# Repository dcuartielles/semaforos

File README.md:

# Aprendiendo electrónica y programación utilizando semáforos
*(título propuesto por La Hora Maker, aka Cesar García)*

Proyecto colectivo de realizar semáforos en la mayor cantidad de modos posible.

*PCB de semáforo por Gustavo Reynaga*

## Lista de Ejemplos

* Jose Antonio Vacas, @javacasm: introducción (aquí forzando)
* Julián Caro Linares, @jcarolinares: FPGA
* David Cuartielles, @dcuartielles: Arduino
* Raúl Lapeira Herrero, @raul_lapeira: Skypic
* Josemanu, @Ardumania_Jmanu: CircuitPython
* Jorge, @akirasan: ATtiny85 + Arduino como programador
* Jorge, @akirasan: Blender
* Jorge, @akirasan: Processing
* Luis Miranda, @LuisMirandaAceb: 555s y componentes discretos
* María L, @tecnoloxia: semáforo mecánico
* María L, @tecnoloxia: Scratch
* David Estévez, @DEFrobotics: RPi + WiringPi
* David Estévez, @DEFrobotics: Semáforo con robot industrial (por los loles)
* Nuria y Jorfru, @nuria_pp: DGT
* Gustavo Reynaga, @gsreynaga: [PCB personalizada con KiCad.](https://github.com/dcuartielles/semaforos/tree/master/ejemplos/KiCad)  [hulkco](https://github.com/hulkco?tab=repositories)
* Iraisy Figueroa, @Iraisy: circuito textil con 555
* Iraisy Figueroa, @Iraisy: S4A
* Alex Corvis, @AlexCorvis84: Node-RED
* Alex Corvis, @AlexCorvis84: MicroPython
* Jose Luis V., @Movilujo: ESP8266
* Raul Tkcheriuk, @RaulTkcheriuk: PLC
* Nerea Iriepa, @nereairiepa: semáforo con servos
* Luis del Valle, @programarfacilc: MKR1000 + Blynk
* Miguel Ángel Abellán, @migueabellan: mBlock
* Victor Barahona, @VictorJBarahona: RaspberryPi3 + Thinger.io   [Egokitek](https://github.com/Egokitek?tab=repositories)
* Manuel Hidalgo, @leobotmanuel: semáforo RGB + ATmega32U4 (Arduino micro)
* Manuel Hidalgo, @leobotmanuel: micro:bit
* Moises Fernandez, @moifdz : ESP8266 con Thingerio [moisesfa](https://github.com/moisesfa?tab=repositories)
* Andrés Sabas, @sabasacustico : Maker MakeCode con Arduino MKR1300 [sabas1080](https://github.com/sabas1080?tab=repositories)
* José Fernando Picó Antolí @JoseFdo_  :FPGA ICE40 de lattice + IDE Icestudio
* Jorge Ramos, @GioSunrider : Semáforo de Competicion
* José Pujol, @Josepujol: Snap4Arduino & EchidnaShield
* Juan González-Gómez @Obijuan: Semáforo en pantalla VGA con FPGA
* Jorge, @akirasan: Free Form Circuit
* Jorge, @akirasan: Badge #NOMÁSSEMÁFOROS

Haz un pull request y añade tu nombre, nick de twitter (si lo tienes), y el proyecto. Si escribes tu nick the github, te haremos contribuidor oficial para no tener que andar jugando con pull-requests después.

## Como contribuir

0. Haz el juramento de Iraisy Figueroa: "Prometo solemnemente no recurrir al semáforo en mis clases, en su lugar buscaré siempre una alternativa mejor, Amén"
1. Haz un pull request del proyecto
2. Dentro de la carpeta ejemplos, crea una carpeta con el nombre de la plataforma sobre la que haras tu ejemplo
3. Crea una subcarpeta "img" donde meter las imágenes, como queremos imprimir esto, usa SVG para poder sacar lo mejor del asunto. Necesitaremos esquemas, dibujos escaneados, ilustraciones con Fritzing, dibujos mecánicos ... lo que sea que uses
4. Crea una subcarpeta "src" y pon ahí el código
5. Si usas un lenguaje de bloques, además de poner el xml o lo que sea que genere tu sistema, haz una captura de pantalla del programa en modo gráfico
6. Crea un Readme.md (usa markdown) y ...
7. Escribe un pequeño párrafo sobre tí misma (unas 100 palabras)
8. Escribe un párrafo sobre la plataforma que has elegido (hasta 500 palabras)
9. Explica tu proyecto (aquí usa lo que necesites, pero se buena, no te pases ... colega)
10. Si eres @javacasm olvida todo lo anterior y escribe una introducción sobre la historia del semáforo

## Licencia

Este manual se presenta bajo [Creative Commons 0](https://creativecommons.org/publicdomain/zero/1.0/) (o dominio público para los amigos) todo el código está bajo [GPLv3](https://www.gnu.org/licenses/gpl-3.0.en.html) a no ser que se diga lo contrario en uno de los ejemplos.

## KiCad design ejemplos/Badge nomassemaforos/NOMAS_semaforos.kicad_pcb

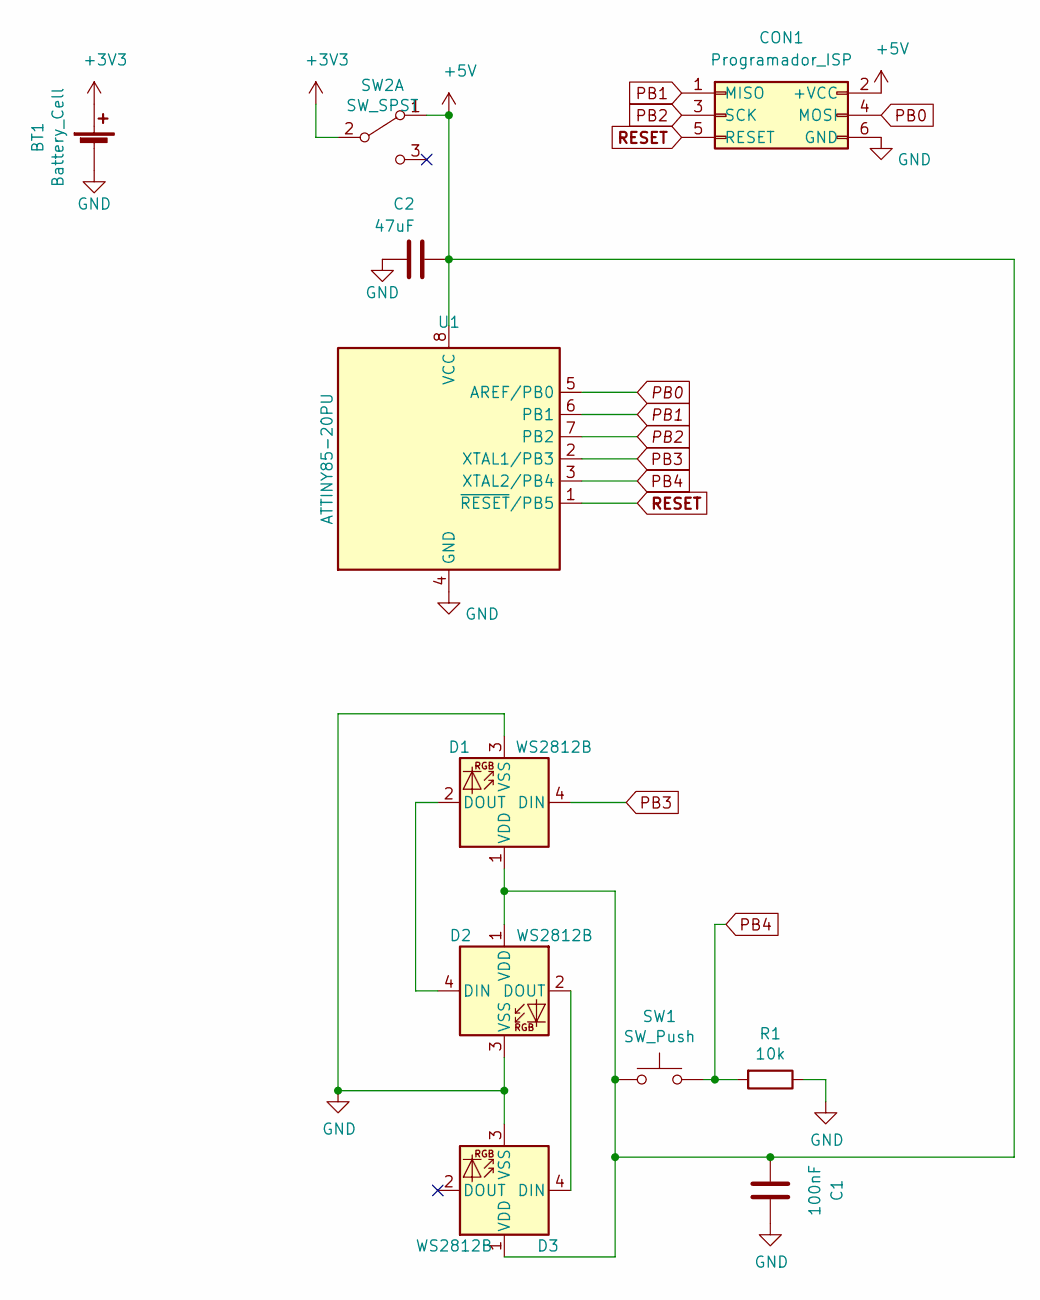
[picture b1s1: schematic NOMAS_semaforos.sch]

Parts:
BT1: Battery_Cell; BatteryHolder_Keystone_3034_1x20mm_MODIFICADA
C1: 100nF; C_0805_2012Metric_Pad1.15x1.40mm_HandSolder
C2: 47uF; C_0805_2012Metric_Pad1.15x1.40mm_HandSolder
CON1: Programador_ISP; ISP_TestPoints
D1, D2, D3: WS2812B; LED_WS2812B_PLCC4_5.0x5.0mm_P3.2mm
R1: 10k; R_0805_2012Metric_Pad1.29x1.40mm_HandSolder
SW1: SW_Push; SW_SPST_TL3342
SW2: SW_SPST; SWITCH_SPST_SMD_A
U1: ATTINY85-20PU; SOIJ-8_5.3x5.3mm_P1.27mm

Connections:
+3V3: BT1.1 (+), SW2.2 (B)
+5V: C1.1, C2.2, CON1.2 (+VCC), D1.1 (VDD), D2.1 (VDD), D3.1 (VDD), SW1.1, SW2.1 (A), U1.8 (VCC)
GND: BT1.2 (-), C1.2, C2.1, CON1.6 (GND), D1.3 (VSS), D2.3 (VSS), D3.3 (VSS), R1.1, U1.4 (GND)
unnamed: D1.2 (DOUT), D2.4 (DIN)
unnamed: D2.2 (DOUT), D3.4 (DIN)
PB0: CON1.4 (MOSI), U1.5 (AREF/PB0)
PB1: CON1.1 (MISO), U1.6 (PB1)
PB2: CON1.3 (SCK), U1.7 (PB2)
PB3: D1.4 (DIN), U1.2 (XTAL1/PB3)
PB4: R1.2, SW1.2, U1.3 (XTAL2/PB4)
RESET: CON1.5 (RESET), U1.1 (~RESET~/PB5)

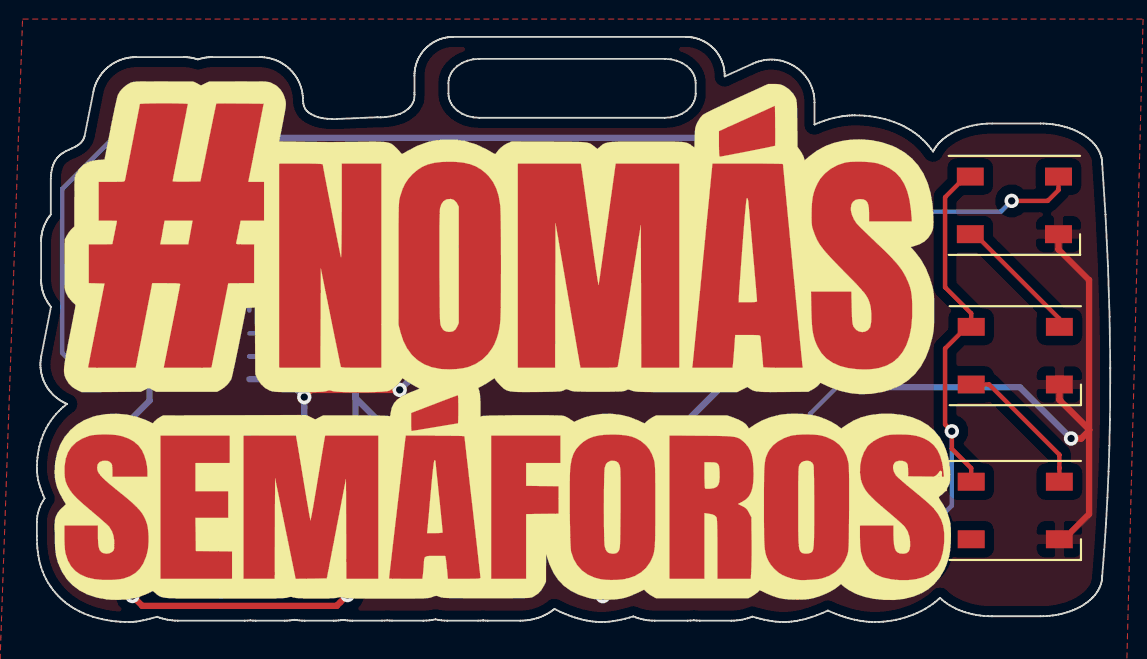
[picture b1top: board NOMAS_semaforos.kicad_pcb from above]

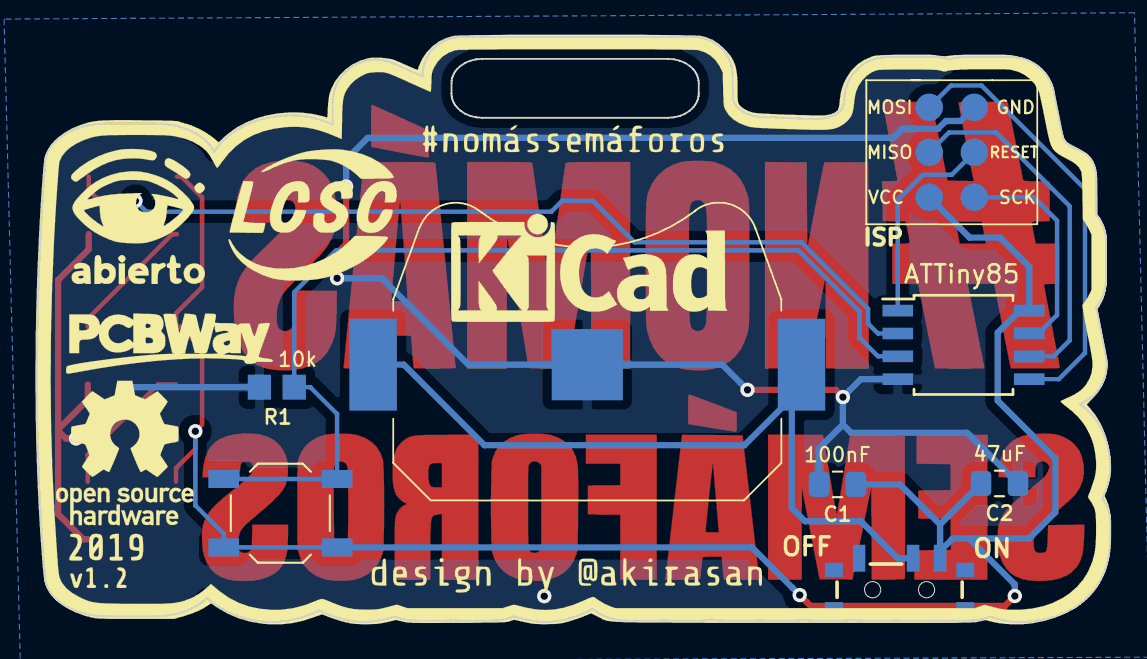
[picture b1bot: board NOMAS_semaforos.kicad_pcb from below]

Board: 2 copper layers, 59.6 x 32.5 mm, 12 parts (8 on the bottom side), 11 nets.

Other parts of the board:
Ref**: Val**; nomassemaforos_v8

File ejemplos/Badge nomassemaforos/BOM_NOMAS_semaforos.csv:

Id,Identificador,Empaquetado,Cantidad,Identificación,Suministrador y ref
2,SW1,TL3342 SW_SPST_TL3342,1,SW_Push,
3,BT1,TBH-CR2032-M04 BatteryHolder_Keystone_3034_1x20mm,1,Battery_Cell,
4,C2,C_0805_2012Metric_Pad1.15x1.40mm_HandSolder,1,47uF,
5,C1,C_0805_2012Metric_Pad1.15x1.40mm_HandSolder,1,100nF,
6,U1,ATTINY85-20SU SOIJ-8_5.3x5.3mm_P1.27mm,1,ATTINY85-20,
7,SW2,MSK-12C02 1P2T SWITCH_SPST_SMD_A,1,SW_SPST,
8,"D1,D2,D3",LED_WS2812B_PLCC4_5.0x5.0mm_P3.2mm Black,3,WS2812B,
10,R1,R_0805_2012Metric_Pad1.29x1.40mm_HandSolder,1,10k,

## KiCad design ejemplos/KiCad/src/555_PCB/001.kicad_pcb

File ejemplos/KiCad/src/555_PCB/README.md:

# Wickerlib.pretty KiCad Module (Footprint) Library
These modules have been edited to have fabrication information for wickerlib. They all come with comments in the headers of each that includes attribution, the appropriate license, and whether the footprint has been used successfully in a project.
It is always the end user's responsibility to verify the package.

This list is updated each time the repository is updated.

Last updated: 20 November 2018

|Module Name|Verified|Finished|
|------|--------|--------|

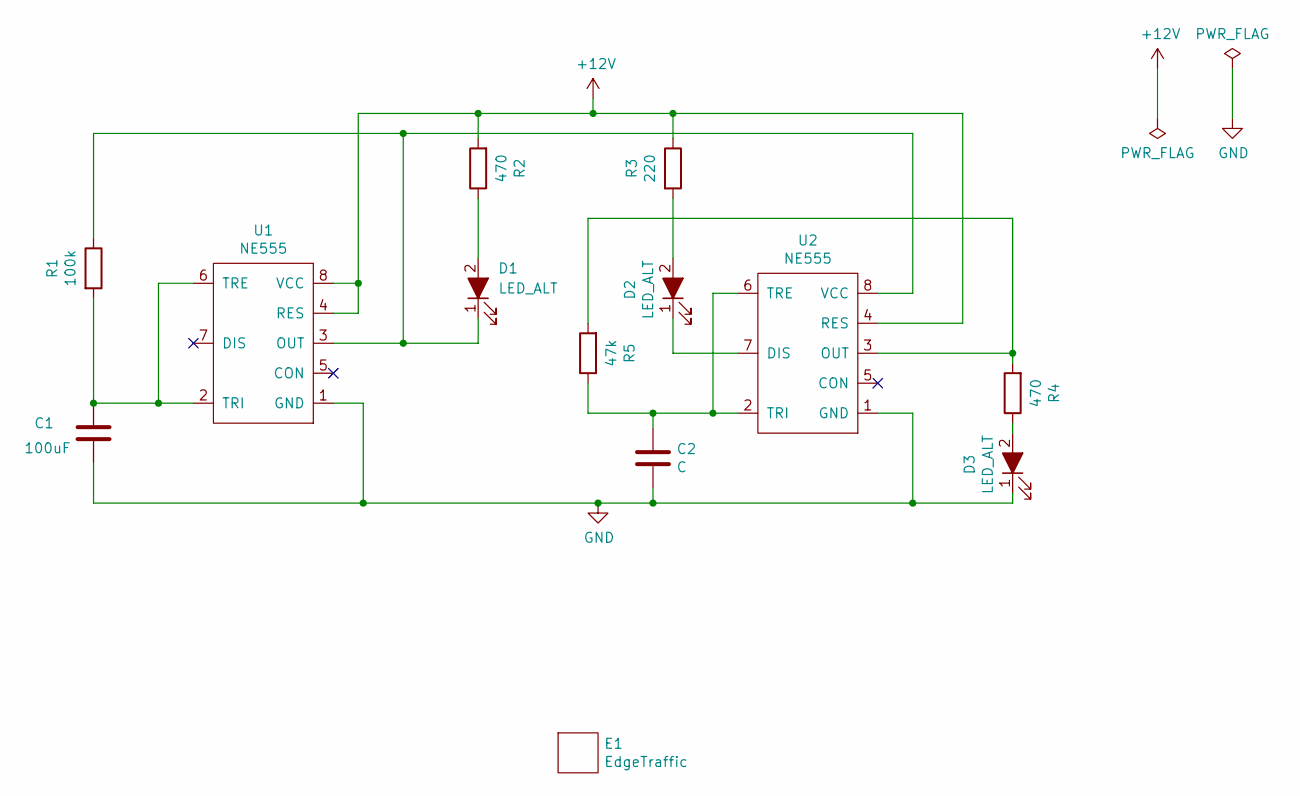
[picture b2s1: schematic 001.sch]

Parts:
C1: 100uF; C_1206_3216Metric_Pad1.39x1.80mm_HandSolder
C2: C; C_1206_3216Metric_Pad1.39x1.80mm_HandSolder
D1, D2, D3: LED_ALT; LED_D10.0mm
E1: EdgeTraffic; 10mm.All.01
R1: 100k; R_1206_3216Metric_Pad1.39x1.80mm_HandSolder
R2, R4: 470; R_1206_3216Metric_Pad1.39x1.80mm_HandSolder
R3: 220; R_1206_3216Metric_Pad1.39x1.80mm_HandSolder
R5: 47k; R_1206_3216Metric_Pad1.39x1.80mm_HandSolder
U1, U2: NE555; SOIC-8-3.9x4.9MM-P1.27MM

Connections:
+12V: R2.2, R3.1, U1.4 (RES), U1.8 (VCC), U2.4 (RES)
GND: C1.1, C2.2, D3.1 (K), U1.1 (GND), U2.1 (GND)
unnamed: C1.2, R1.2, U1.2 (TRI), U1.6 (TRE)
unnamed: C2.1, R5.1, U2.2 (TRI), U2.6 (TRE)
unnamed: D1.1 (K), R1.1, U1.3 (OUT), U2.8 (VCC)
unnamed: D1.2 (A), R2.1
unnamed: D2.1 (K), U2.7 (DIS)
unnamed: D2.2 (A), R3.2
unnamed: D3.2 (A), R4.1
unnamed: R4.2, R5.2, U2.3 (OUT)

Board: 2 copper layers, 13 parts (9 on the bottom side), 10 nets, no tracks yet.

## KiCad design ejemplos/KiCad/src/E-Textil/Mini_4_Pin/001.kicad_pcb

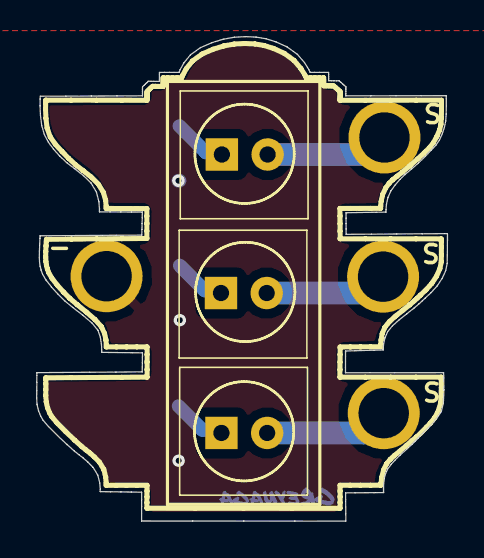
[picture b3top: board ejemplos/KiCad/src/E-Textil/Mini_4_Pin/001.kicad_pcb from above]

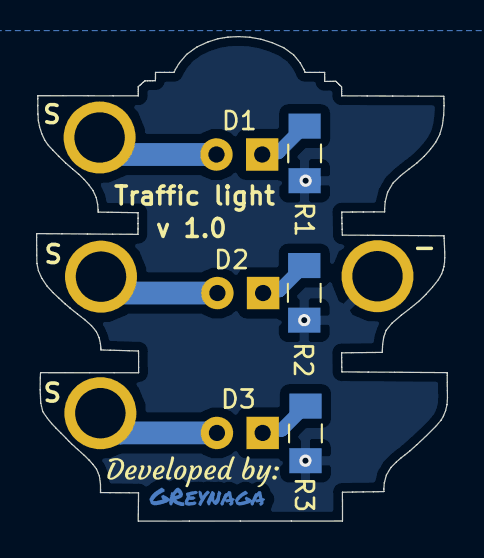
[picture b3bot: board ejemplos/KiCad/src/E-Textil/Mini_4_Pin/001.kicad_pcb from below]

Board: 2 copper layers, 22.8 x 26.9 mm, 13 parts (5 on the bottom side), 7 nets.

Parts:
D1, D2, D3: LED_ALT; LED_D3.0mm
E1: EdgeTraffic; Semaforo2.All.02
J2, J4, J5, J6: CONN_01X01; Pad_02
R1, R2, R3: 330; R_1206_3216Metric_Pad1.39x1.80mm_HandSolder
svg2mod: G***; GReynaga.CuMask3
svg2mod#2: G***; Developed-Silks3

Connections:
GND: J2.1, R1.2, R2.2, R3.2
unnamed: D1.1, R1.1
unnamed: D1.2, J4.1
unnamed: D2.1, R2.1
unnamed: D2.2, J5.1
unnamed: D3.1, R3.1
unnamed: D3.2, J6.1

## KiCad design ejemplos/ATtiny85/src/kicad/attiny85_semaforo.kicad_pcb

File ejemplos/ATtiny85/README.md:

# ATtiny85 + Programador ISP Arduino

Este es el ejemplo de cómo programar un semáforo sencillo mediante...

## Sobre el autor

Me llamo Jorge, aunque algunos me conocen como @akirasan. Desde que en 2011 conocí Arduino no he querido parar de aprender, y para aprender utilizo una técnica muy sencilla: construir cosas. Manteniendo la curiosidad por saber cómo funcionan las cosas. Y Arduino me abrió una puerta a la electrónica digital. Un mundo que desconocía casi por completo, ya que siempre he estado mas enfocado al software abierto, pero no al hardware abierto.

A nivel personal soy miembro (me tienen puesto de presidente) de una comunidad de Makers llamada Ripola Hacklab, dónde hacemos divulgación de la tecnología a la Comunidad Educativa. Buscamos hacer cosas chulas para que las familias construyan y aprendan juntas.

## Porqué esta plataforma

He utilizado ATtiny85 en algunos proyectos sobretodo para desarrollar placas PCBs que requieren de algún tipo de interacción. Me parece una solución sencilla y muy práctica para aquellos, que cómo yo, no sabemos mucho de electrónica y algo si de programación.

Para su programación he utilizado el IDE de Arduino, que está muy extendido y es muy sencillo para implementar soluciones con electrónica digital. 

## Cómo y porqué de tu proyecto

El "cómo y porqué" del proyecto es claro: Nos calentamos muy rápido por Twitter.
Soy muy fan del hashtag [#NoMásSemáforos][3]. Creo que se pueden aprender y hacer muchas cosas chulas, mas allá de los semáforos (que viene a ser el tipico ejemplo recurrente y poco atractivo).

[1]: https://www.akirasan.net
[2]: https://github.com/akirasan
[3]: https://twitter.com/hashtag/nomassemaforos

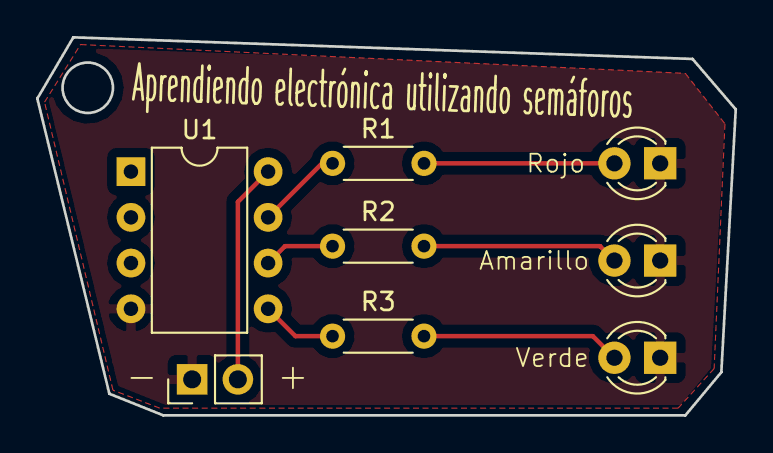
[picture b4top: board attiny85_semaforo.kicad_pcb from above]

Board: 2 copper layers, 38.8 x 21.0 mm, 8 parts (0 on the bottom side), 8 nets.

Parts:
D1, D2, D3: LED; LED_D3.0mm_FlatTop
J1: Conn_01x02; PinHeader_1x02_P2.54mm_Vertical
R1, R2, R3: R; R_Axial_DIN0204_L3.6mm_D1.6mm_P5.08mm_Horizontal
U1: ATtiny85-20PU; DIP-8_W7.62mm

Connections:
+5V: J1.2, U1.8
GND: D1.1, D2.1, D3.1, J1.1, U1.4
unnamed: D1.2, R1.2
unnamed: D2.2, R2.2
unnamed: D3.2, R3.2
unnamed: R1.1, U1.7
unnamed: R2.1, U1.6
unnamed: R3.1, U1.5

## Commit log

2018-11-12 Add mblock
2018-11-12 Add autor Miguel Ángel Abellán README.md
2018-11-12 Update link README
2018-11-12 Add description
2018-11-13 Create mkr1000 blynk project
    Add Readme.md and sketch finished
2018-11-13 Firts upload
2018-11-13 Add new image
    Add imagre from electric circuit in Fritzing
2018-11-13 Propuesta nuevo título
    He añadido programación ya que es una parte importante que deben de
    aprender para llevar a buen puerto los proyectos de los semáforos.
2018-11-13 Placa MKR1000
    Al final lo hago con MKR1000
2018-11-13 Upload KiCad Files
2018-11-13 Auto stash before merge of "master" and "origin/master"
2018-11-13 Update Reame
2018-11-13 Update Readmes en PCBs
2018-11-13 Update Readme in Parent
2018-11-13 Rename ejemplos/semaforo.py to ejemplos/CircuitPython/semaforo.py
2018-11-13 Initial examples
2018-11-14 Create Readme.md
    Creada la carpeta ESP8266
2018-11-14 Añadido código ejemplo
2018-11-14 Added new examples-pedestrian lights+sounds
2018-11-14 imagenes
2018-11-15 Modificado el Readme
2018-11-16 muevo dir por error
2018-11-16 Documentación proyecto
    Modificado el Readme.md del proyecto, añadido fotos y mejorar del código
    con comentarios.
2018-11-18 Create MicroPython
2018-11-19 Rename semaforo_NeoPixel16LED.py to main.py
2018-11-19 Corregida ruta imágenes
    Corregida ruta imágenes
2018-11-19 Create Node-RED
2018-11-19 Create Formatted JSON flows
2018-11-19 Create Compact JSON flows
2018-11-19 Add Universal PCB 10mm Semaforo
2018-11-19 Ejemplo Esp8266 con Thingerio
2018-11-20 Add PCB for 555 and Atiny85
2018-11-23 Blender 3D
2018-11-23 Add Makecode example
    :v
2018-11-24 Nuevas imagenes
2018-11-26 correccion carpeta
2018-11-28 Add Universal 4 Pin PCB
2018-11-28 Update Readme in Kicad
2018-11-28 Update Readme in parent new PCB Universal
2018-11-29 Some minors updates
2018-11-29 Readme final
2018-11-30 IceSutudio FPGA Neopixel
    Creación de semáforo con IDE IceStudio usando FPGA IceStick ( ICE40 1k )
    y panel de 8x8 leds Neopixel.
2018-11-30 Corrección y añadir juramento
2018-11-30 Update README
    Actualización README.md principal
2018-12-08 Some updates
2018-12-24 Initial project files
2018-12-24 Alhambra-FPGA-VGA updated
2018-12-24 Alhambra-FPGA-VGA: New image added
2018-12-24 Alhambra-VGA-FPGA: README updted
2018-12-24 Alhambra-VGA-FPGA: Readme updated
2018-12-24 Added the FPGA-VGA light traffic contribution
2019-01-12 First update
2019-01-12 Retoques en el fichero README
2019-01-12 Retoques en el README
2019-01-12 Codigo fuente actulizado
2019-01-12 Cambio de nombre de la carpeta Source a SRC
2019-01-12 Create a
2019-01-13 Añadido proyecto Ultibo-TFT
2019-01-13 Modificado README.md. Se le añade un enlace a un vídeo en youtube
2019-04-29 Creado fichero de referencias
2019-04-29 Historia de los reguladores de trafico aka semaforos
2019-07-08 Free Form
